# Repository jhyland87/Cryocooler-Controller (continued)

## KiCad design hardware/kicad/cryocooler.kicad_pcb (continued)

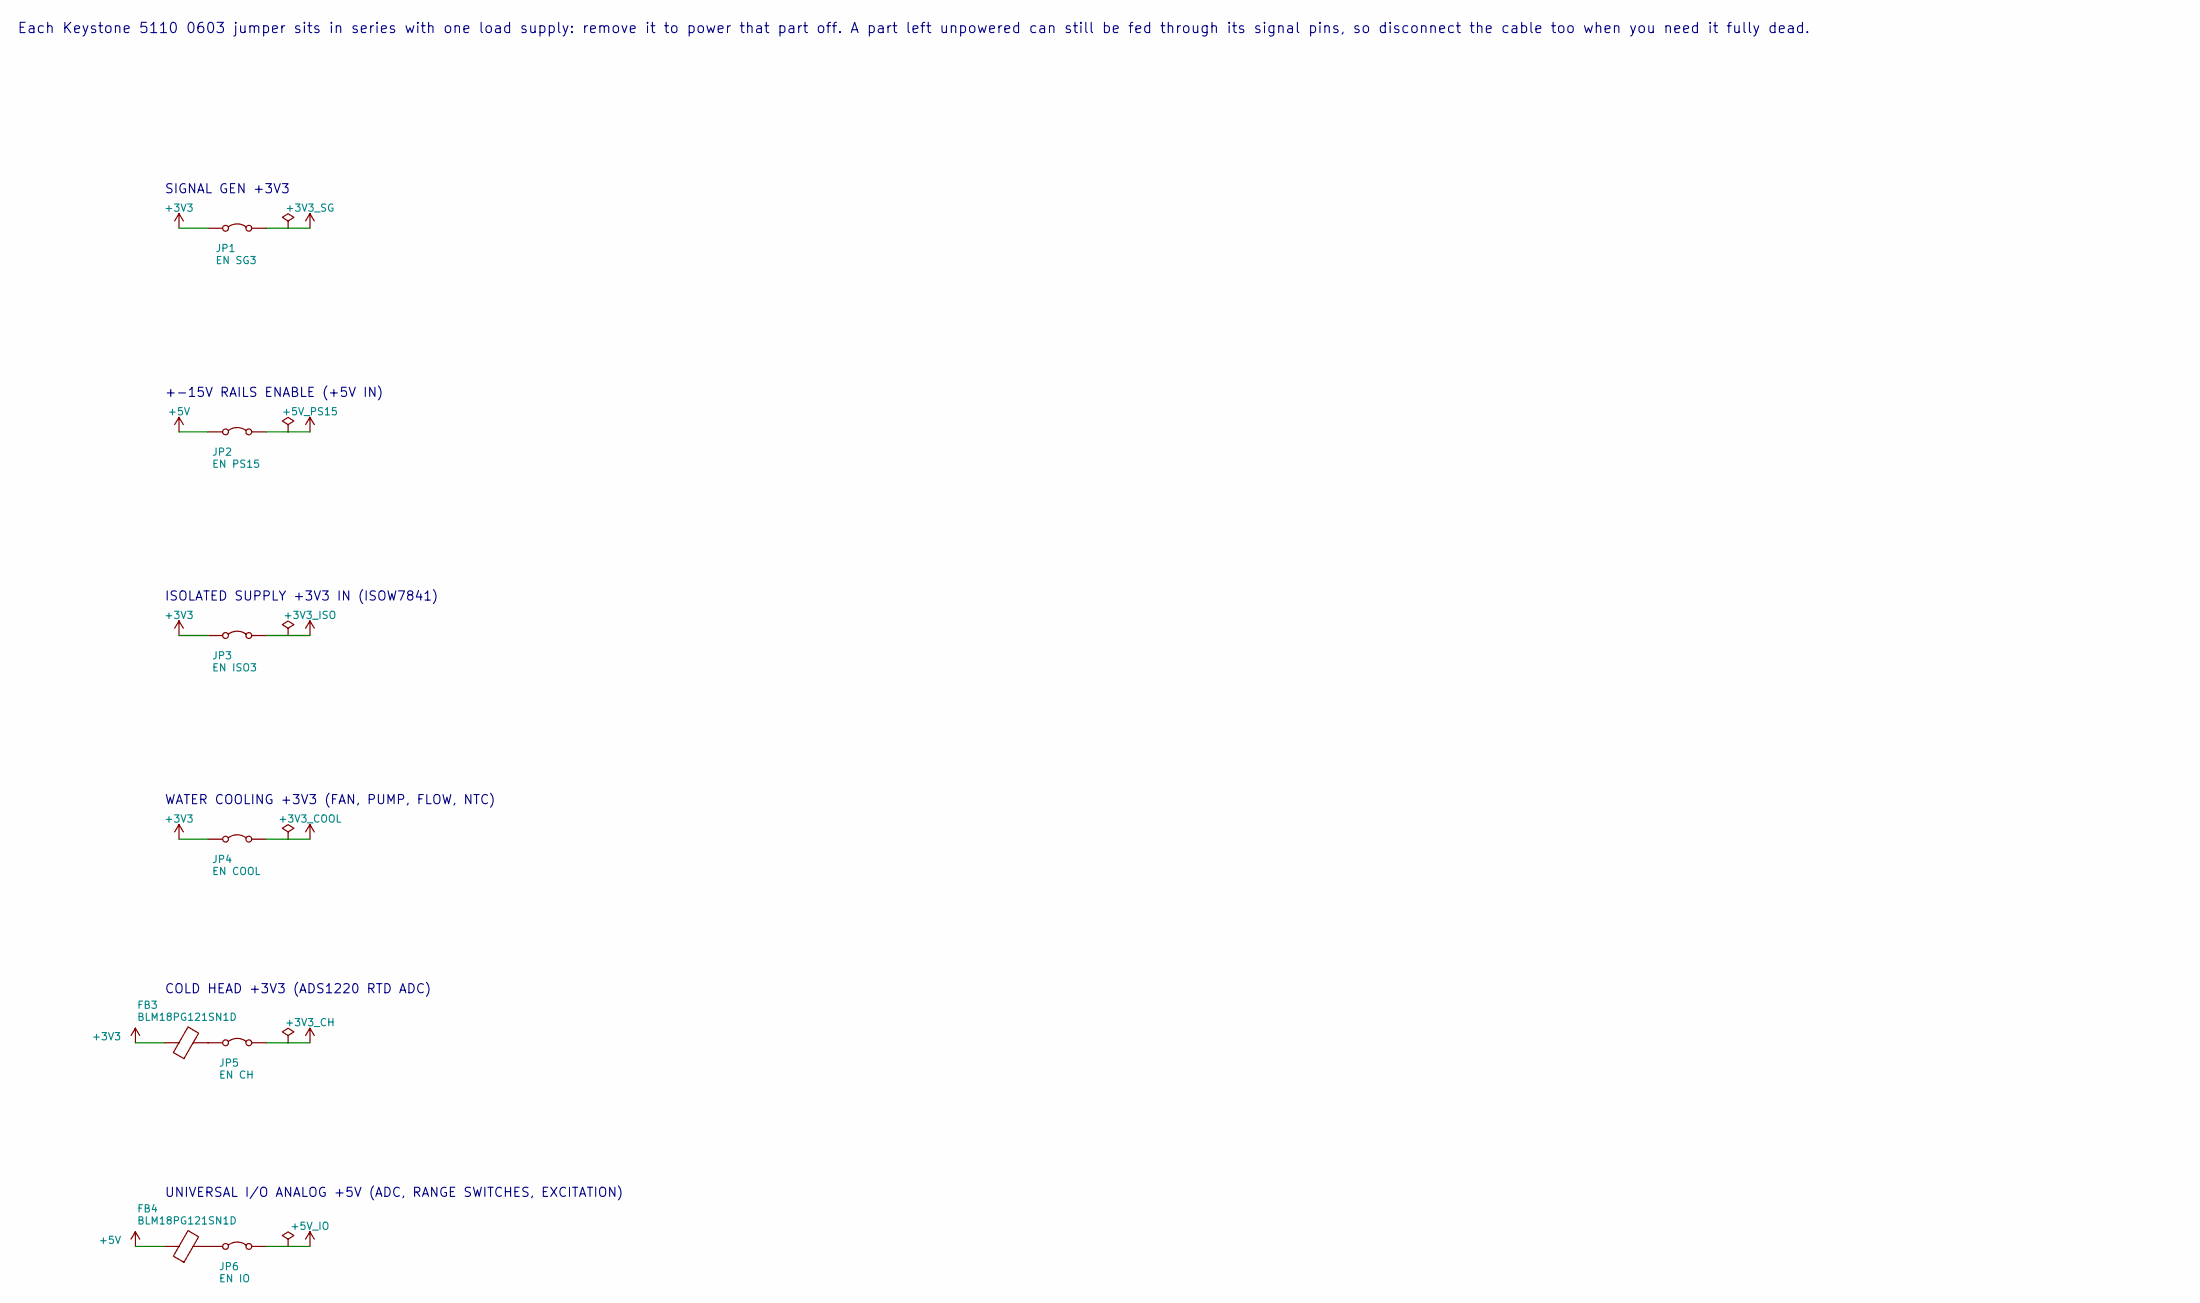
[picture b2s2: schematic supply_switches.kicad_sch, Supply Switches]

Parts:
FB3, FB4: BLM18PG121SN1D; L_0603_1608Metric
JP1: EN SG3; R_0603_1608Metric
JP2: EN PS15; R_0603_1608Metric
JP3: EN ISO3; R_0603_1608Metric
JP4: EN COOL; R_0603_1608Metric
JP5: EN CH; R_0603_1608Metric
JP6: EN IO; R_0603_1608Metric

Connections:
+3V3: FB3.1, JP1.1 (A), JP3.1 (A), JP4.1 (A); also elsewhere on the board
+3V3_CH: JP5.2 (B); also elsewhere on the board
+3V3_COOL: JP4.2 (B); also elsewhere on the board
+3V3_ISO: JP3.2 (B); also elsewhere on the board
+3V3_SG: JP1.2 (B); also elsewhere on the board
+5V: FB4.1, JP2.1 (A); also elsewhere on the board
+5V_IO: JP6.2 (B); also elsewhere on the board
+5V_PS15: JP2.2 (B); also elsewhere on the board
unnamed: FB3.2, JP5.1 (A)
unnamed: FB4.2, JP6.1 (A)

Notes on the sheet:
ISOLATED SUPPLY +3V3 IN (ISOW7841)
+-15V RAILS ENABLE (+5V IN)
Each Keystone 5110 0603 jumper sits in series with one load supply: remove it to power that part off. A part left unpowered can still be fed through its signal pins, so disconnect the cable too when you need it fully dead.
SIGNAL GEN +3V3
WATER COOLING +3V3 (FAN, PUMP, FLOW, NTC)
COLD HEAD +3V3 (ADS1220 RTD ADC)
UNIVERSAL I/O ANALOG +5V (ADC, RANGE SWITCHES, EXCITATION)

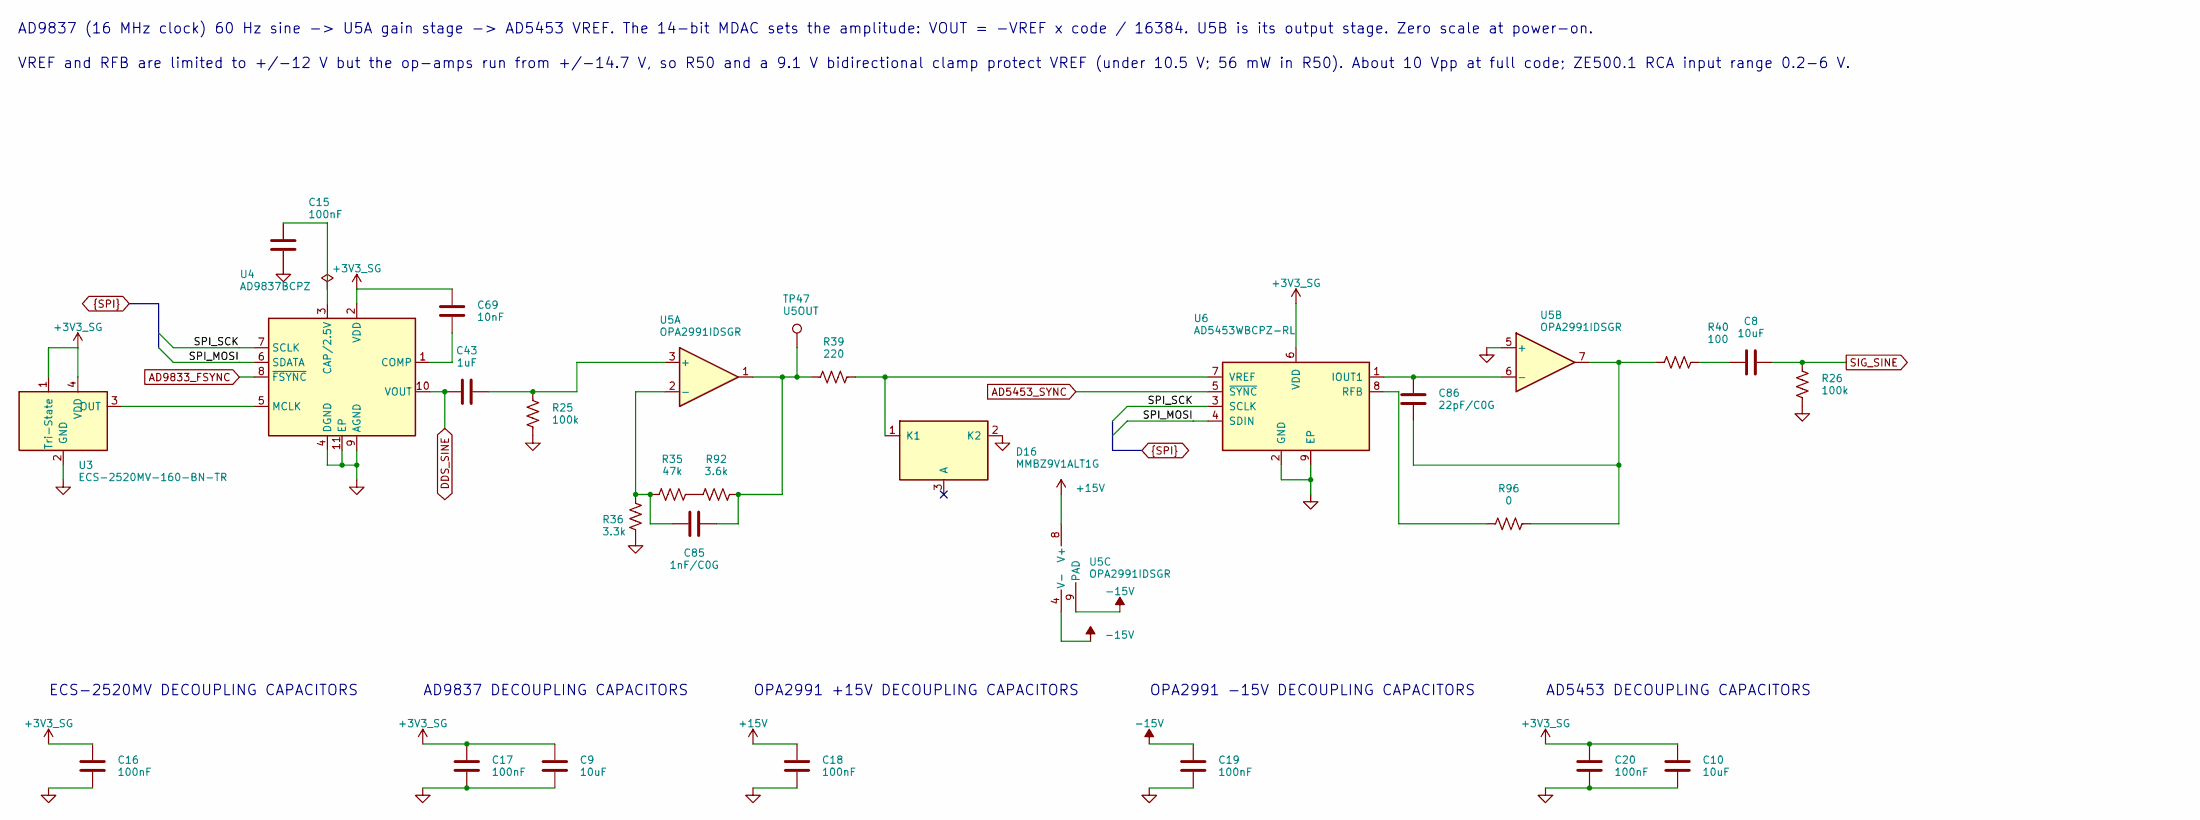
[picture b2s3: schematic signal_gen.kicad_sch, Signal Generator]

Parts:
C8, C9, C10: 10uF; C_0805_2012Metric
C15, C16, C17, C18, C19, C20: 100nF; C_0402_1005Metric
C43: 1uF; C_0603_1608Metric
C69: 10nF; C_0402_1005Metric
C85: 1nF/C0G; C_0402_1005Metric
C86: 22pF/C0G; C_0402_1005Metric
D16: MMBZ9V1ALT1G; SOT-23
R25, R26: 100k; R_0402_1005Metric
R35: 47k; R_0402_1005Metric
R36: 3.3k; R_0402_1005Metric
R39: 220; R_0402_1005Metric
R40: 100; R_0402_1005Metric
R92: 3.6k; R_1206_or_Bourns_3313J
R96: 0; R_1206_or_Bourns_3313J
TP47: U5OUT; TestPoint_Pad_D1.0mm
U3: ECS-2520MV-160-BN-TR; Oscillator_SMD_ECS_2520MV-xxx-xx-4Pin_2.5x2.0mm
U4: AD9837BCPZ; LFCSP-WD-10-1EP_3x3mm_P0.5mm_EP1.64x2.38mm
U5: OPA2991IDSGR; TI_DSG0008A_WSON-8-1EP_2x2mm_P0.5mm_EP0.9x1.6mm
U6: AD5453WBCPZ-RL; VSON-8-1EP_3x3mm_P0.65mm_EP1.65x2.4mm

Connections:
+3V3_SG: C9.1, C10.1, C16.1, C17.1, C20.1, C69.1, U3.1 (Tri-State), U3.4 (VDD), U4.2 (VDD), U6.6 (VDD); also elsewhere on the board
+15V: C18.1, U5.8 (V+); also elsewhere on the board
-15V: C19.1, U5.4 (V-), U5.9 (PAD); also elsewhere on the board
/DDS_SINE: C43.1, U4.10 (VOUT); also elsewhere on the board
/SIG_SINE: C8.2, R26.1; also elsewhere on the board
/~AD5453_SYNC: U6.5 (~SYNC); also elsewhere on the board
/~AD9833_FSYNC: U4.8 (~FSYNC); also elsewhere on the board
GND: C9.2, C10.2, C15.2, C16.2, C17.2, C18.2, C19.2, C20.2, D16.2 (K2), R25.2, R26.2, R36.2, U3.2 (GND), U4.4 (DGND), U4.9 (AGND), U4.11 (EP), U5.5 (+), U6.2 (GND), U6.9 (EP); also elsewhere on the board
unnamed: C8.1, R40.2
unnamed: C85.2, R39.1, R92.2, TP47.1, U5.1
unnamed: C86.2, R40.1, R96.2, U5.7
unnamed: D16.1 (K1), R39.2, U6.7 (VREF)
unnamed: R35.2, R92.1
unnamed: U3.3 (OUT), U4.5 (MCLK)
unnamed: C15.1, U4.3 (CAP/2.5V)
unnamed: C69.2, U4.1 (COMP)
unnamed: C43.2, R25.1, U5.3 (+)
unnamed: C85.1, R35.1, R36.1, U5.2 (-)
unnamed: C86.1, U5.6 (-), U6.1 (IOUT1)
unnamed: R96.1, U6.8 (RFB)
SPI_MOSI: U4.6 (SDATA), U6.4 (SDIN); also elsewhere on the board
SPI_SCK: U4.7 (SCLK), U6.3 (SCLK); also elsewhere on the board

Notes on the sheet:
OPA2991 +15V DECOUPLING CAPACITORS
AD9837 (16 MHz clock) 60 Hz sine -> U5A gain stage -> AD5453 VREF. The 14-bit MDAC sets the amplitude: VOUT = -VREF x code / 16384. U5B is its output stage. Zero scale at power-on.
AD9837 DECOUPLING CAPACITORS
VREF and RFB are limited to +/-12 V but the op-amps run from +/-14.7 V, so R50 and a 9.1 V bidirectional clamp protect VREF (under 10.5 V; 56 mW in R50). About 10 Vpp at full code; ZE500.1 RCA input range 0.2-6 V.
ECS-2520MV DECOUPLING CAPACITORS
AD5453 DECOUPLING CAPACITORS
OPA2991 -15V DECOUPLING CAPACITORS

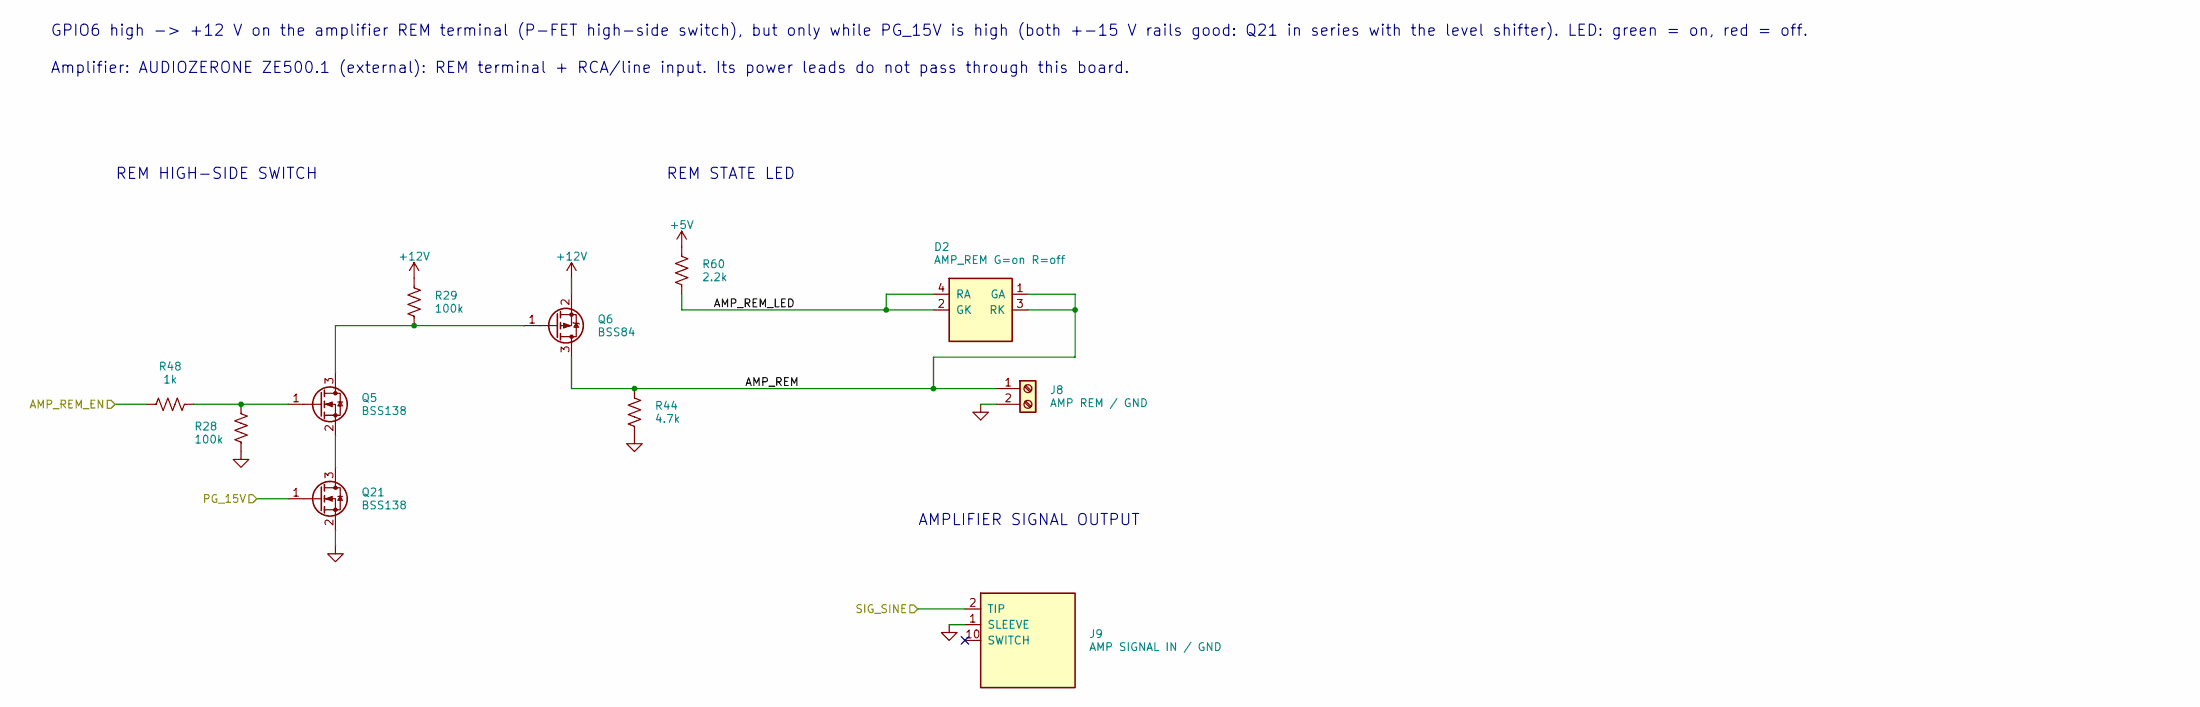
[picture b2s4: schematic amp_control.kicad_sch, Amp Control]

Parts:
D2: AMP_REM G=on R=off; LED_Kingbright_APGB0607
J8: AMP REM / GND; PhoenixContact_MC_0,5_2-G-2,54_SMD_1x02_P2.54mm_Horizontal
J9: AMP SIGNAL IN / GND; SameSky_MJ-3523-SMT-TR_3.5mm_Horizontal_SMD
Q5, Q21: BSS138; SOT-23
Q6: BSS84; SOT-23
R28, R29: 100k; R_0402_1005Metric
R44: 4.7k; R_0402_1005Metric
R48: 1k; R_0402_1005Metric
R60: 2.2k; R_0402_1005Metric

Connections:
+5V: R60.1; also elsewhere on the board
+12V: Q6.2 (S), R29.1; also elsewhere on the board
/AMP_REM_EN: R48.1; also elsewhere on the board
/Amp Control/AMP_REM: D2.1 (GA), D2.3 (RK), J8.1, Q6.3 (D), R44.1
/Amp Control/AMP_REM_LED: D2.2 (GK), D2.4 (RA), R60.2
/PG_15V: Q21.1 (G); also elsewhere on the board
/SIG_SINE: J9.2 (TIP); also elsewhere on the board
GND: J8.2, J9.1 (SLEEVE), Q21.2 (S), R28.2, R44.2; also elsewhere on the board
unnamed: Q5.3 (D), Q6.1 (G), R29.2
unnamed: Q5.1 (G), R28.1, R48.2
unnamed: Q5.2 (S), Q21.3 (D)

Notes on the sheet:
GPIO6 high -> +12 V on the amplifier REM terminal (P-FET high-side switch), but only while PG_15V is high (both +-15 V rails good: Q21 in series with the level shifter). LED: green = on, red = off.
REM HIGH-SIDE SWITCH
AMPLIFIER SIGNAL OUTPUT
REM STATE LED
Amplifier: AUDIOZERONE ZE500.1 (external): REM terminal + RCA/line input. Its power leads do not pass through this board.

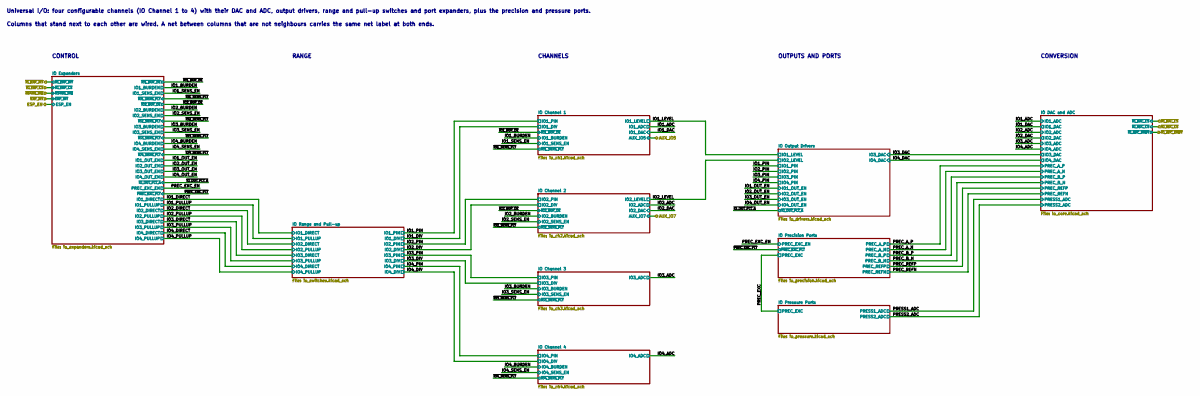
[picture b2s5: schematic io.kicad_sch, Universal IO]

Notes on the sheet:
Columns that stand next to each other are wired. A net between columns that are not neighbours carries the same net label at both ends.
Universal I/O: four configurable channels (IO Channel 1 to 4) with their DAC and ADC, output drivers, range and pull-up switches and port expanders, plus the precision and pressure ports.
CHANNELS
OUTPUTS AND PORTS
RANGE
CONVERSION
CONTROL

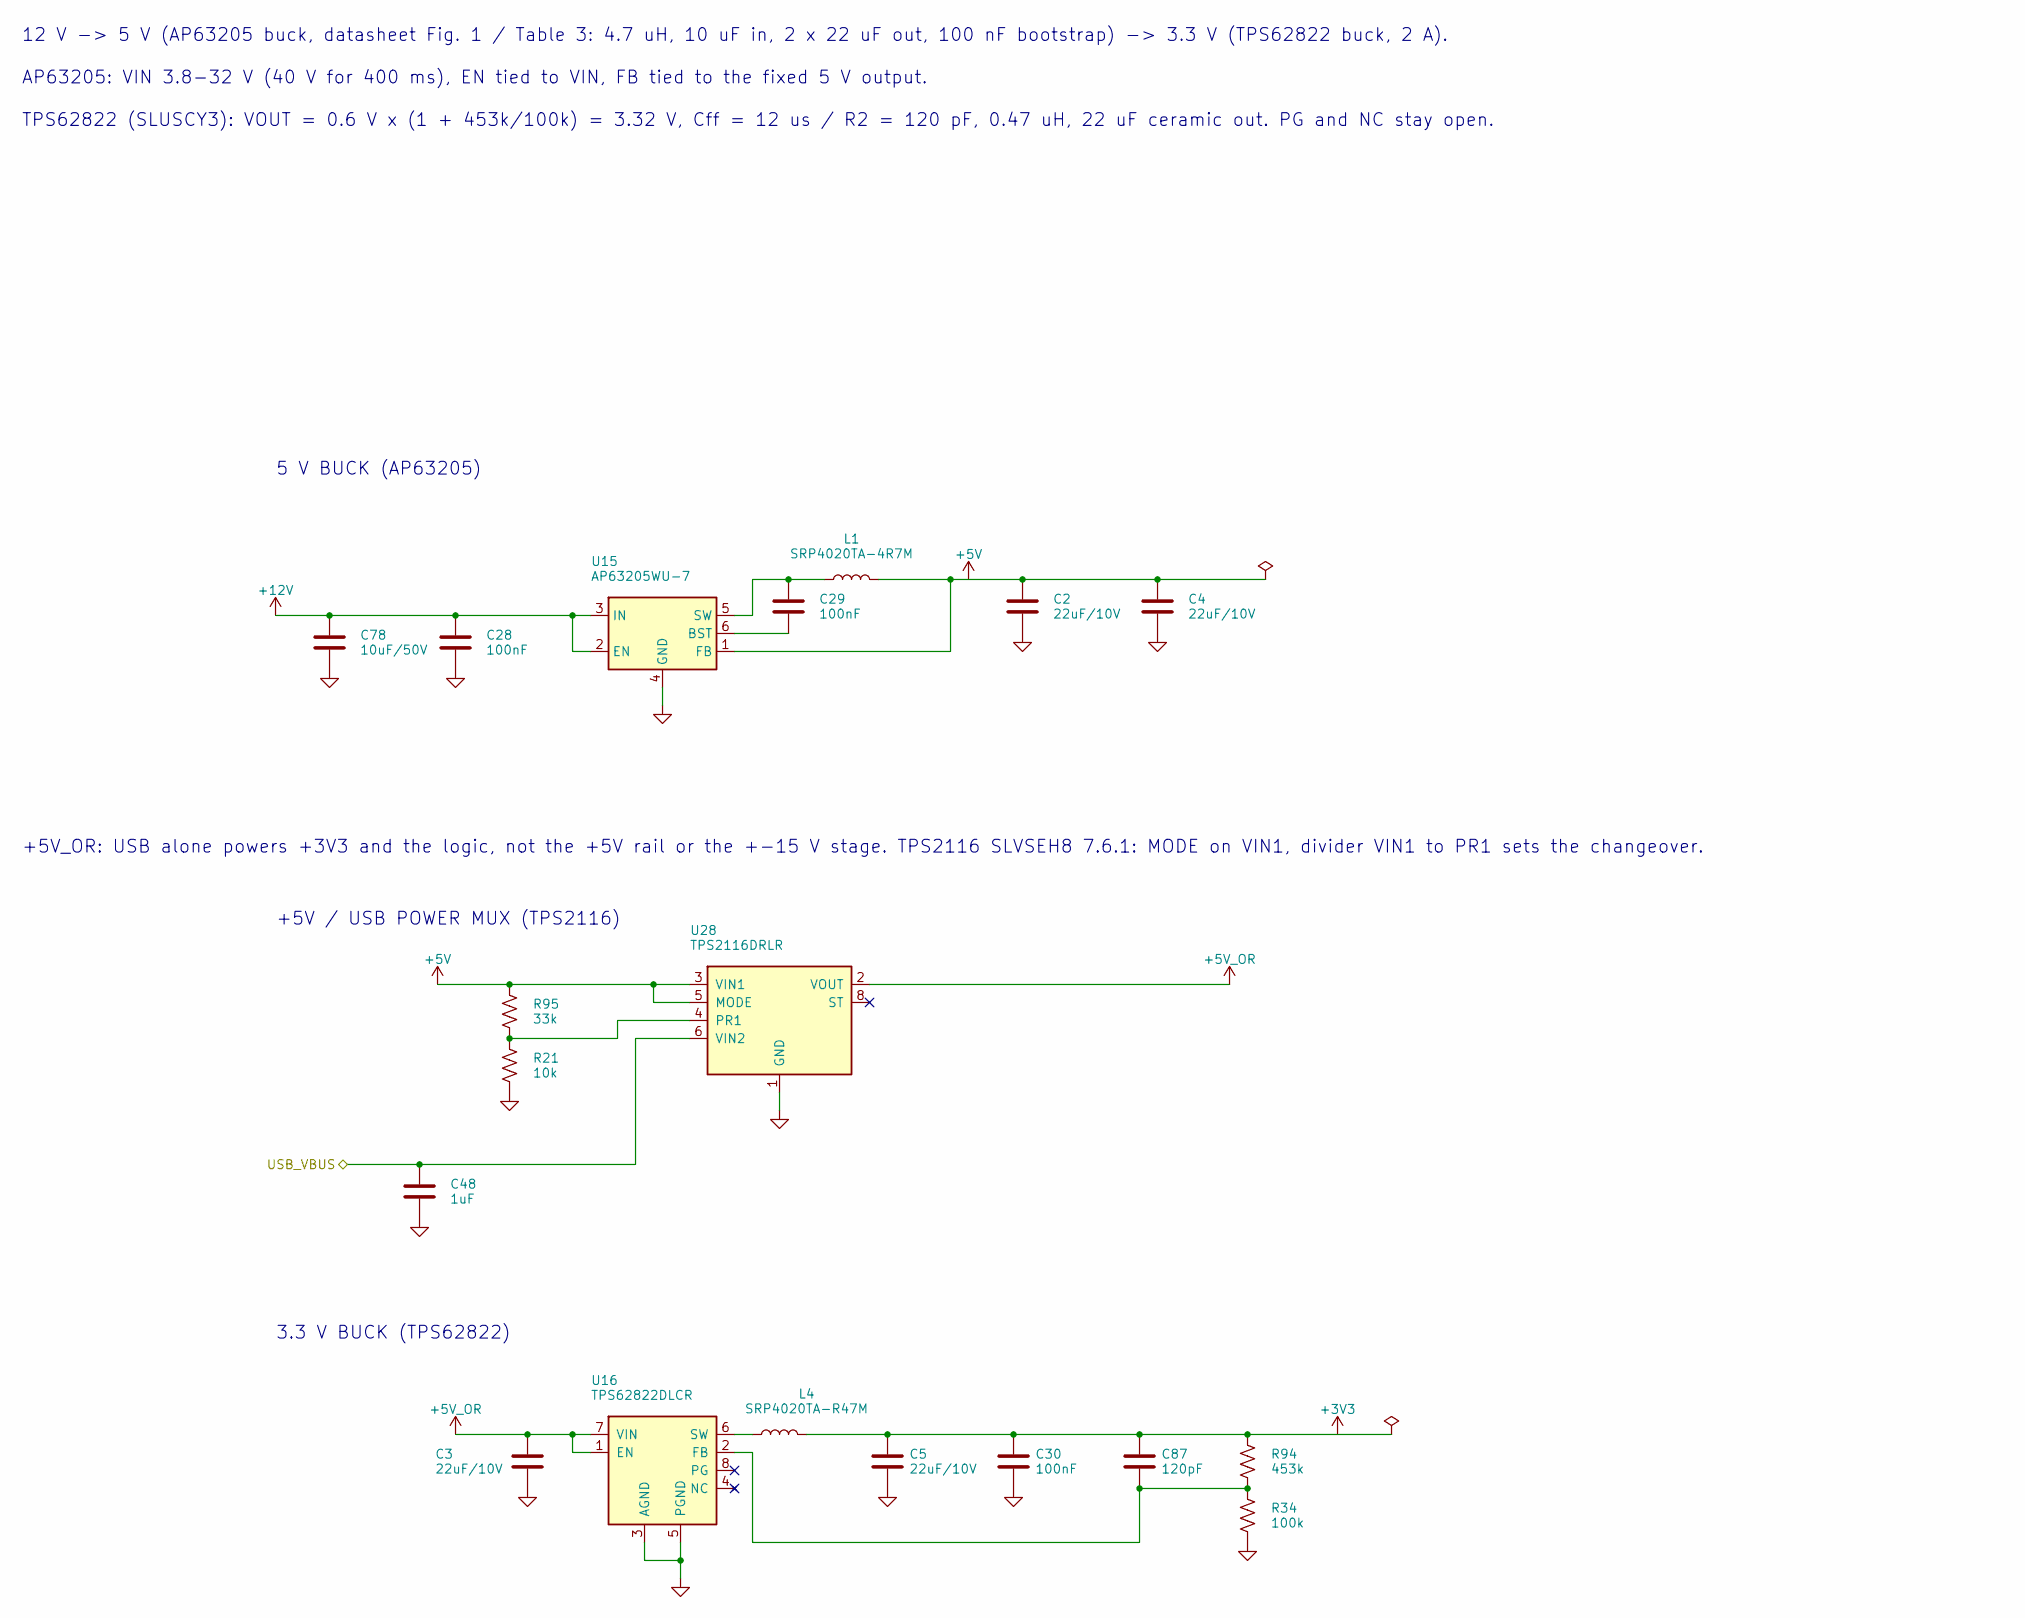
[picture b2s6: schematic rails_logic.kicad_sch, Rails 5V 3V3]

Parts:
C2, C3, C4, C5: 22uF/10V; C_1206_3216Metric
C28, C29, C30: 100nF; C_0402_1005Metric
C48: 1uF; C_0603_1608Metric
C78: 10uF/50V; C_1206_3216Metric
C87: 120pF; C_0402_1005Metric
L1: SRP4020TA-4R7M; L_Bourns_SRP4020TA
L4: SRP4020TA-R47M; L_Bourns_SRP4020TA
R21: 10k; R_0402_1005Metric
R34: 100k; R_0402_1005Metric
R94: 453k; R_0402_1005Metric
R95: 33k; R_0402_1005Metric
U15: AP63205WU-7; TSOT-23-6
U16: TPS62822DLCR; Texas_VSON-HR-8_1.5x2mm_P0.5mm
U28: TPS2116DRLR; SOT-583-8

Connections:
+3V3: C5.1, C30.1, C87.1, L4.2, R94.1; also elsewhere on the board
+5V: C2.1, C4.1, L1.2, R95.1, U15.1 (FB), U28.3 (VIN1), U28.5 (MODE); also elsewhere on the board
+5V_OR: C3.1, U16.1 (EN), U16.7 (VIN), U28.2 (VOUT), U28.7 (VOUT)
+12V: C28.1, C78.1, U15.2 (EN), U15.3 (IN); also elsewhere on the board
/USB_VBUS: C48.1, U28.6 (VIN2); also elsewhere on the board
GND: C2.2, C3.2, C4.2, C5.2, C28.2, C30.2, C48.2, C78.2, R21.2, R34.2, U15.4 (GND), U16.3 (AGND), U16.5 (PGND), U28.1 (GND); also elsewhere on the board
unnamed: C29.2, U15.6 (BST)
unnamed: C29.1, L1.1, U15.5 (SW)
unnamed: C87.2, R34.1, R94.2, U16.2 (FB)
unnamed: L4.1, U16.6 (SW)
unnamed: R21.1, R95.2, U28.4 (PR1)

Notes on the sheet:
+5V / USB POWER MUX (TPS2116)
TPS62822 (SLUSCY3): VOUT = 0.6 V x (1 + 453k/100k) = 3.32 V, Cff = 12 us / R2 = 120 pF, 0.47 uH, 22 uF ceramic out. PG and NC stay open.
AP63205: VIN 3.8-32 V (40 V for 400 ms), EN tied to VIN, FB tied to the fixed 5 V output.
5 V BUCK (AP63205)
3.3 V BUCK (TPS62822)
12 V -> 5 V (AP63205 buck, datasheet Fig. 1 / Table 3: 4.7 uH, 10 uF in, 2 x 22 uF out, 100 nF bootstrap) -> 3.3 V (TPS62822 buck, 2 A).
+5V_OR: USB alone powers +3V3 and the logic, not the +5V rail or the +-15 V stage. TPS2116 SLVSEH8 7.6.1: MODE on VIN1, divider VIN1 to PR1 sets the changeover.

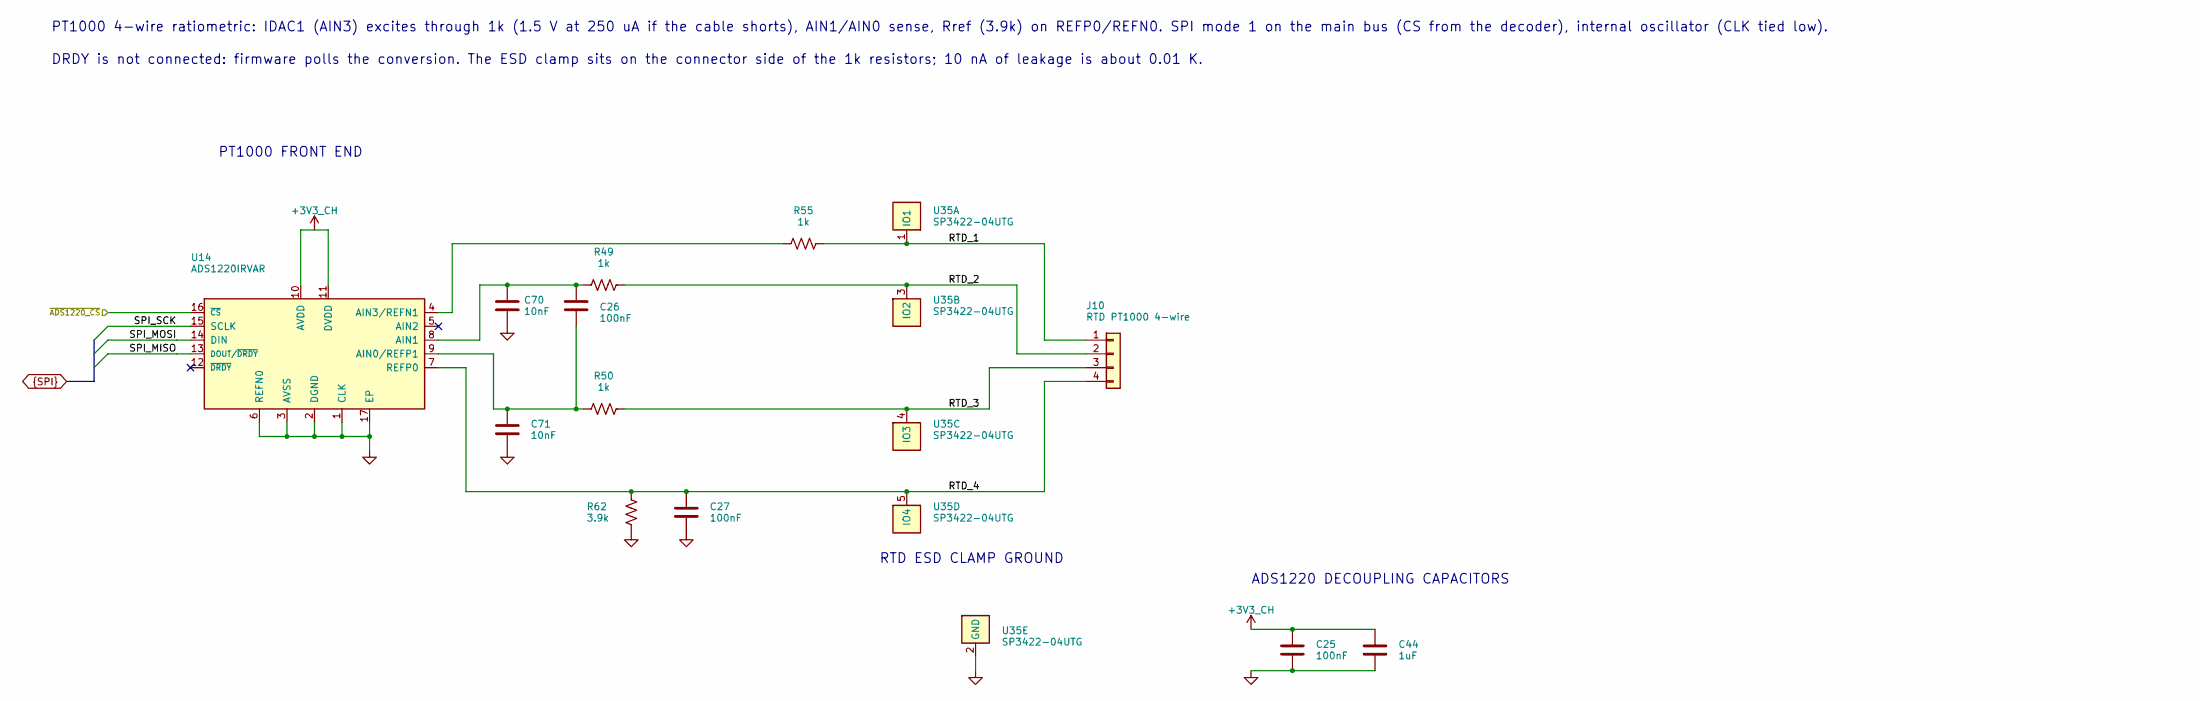
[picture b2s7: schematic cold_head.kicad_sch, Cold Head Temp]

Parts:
C25, C26, C27: 100nF; C_0402_1005Metric
C44: 1uF; C_0603_1608Metric
C70, C71: 10nF; C_0402_1005Metric
J10: RTD PT1000 4-wire; Adafruit_4392_JST-PH_1x04_P2.00mm_Horizontal_SMD
R49, R50, R55: 1k; R_0402_1005Metric
R62: 3.9k; R_0402_1005Metric
U14: ADS1220IRVAR; Texas_RVA_VQFN-16-1EP_3.5x3.5mm_P0.5mm_EP2.14x2.14mm
U35: SP3422-04UTG; Littelfuse_DFN-5_1.0x0.6mm_P0.35mm

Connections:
+3V3_CH: C25.1, C44.1, U14.10 (AVDD), U14.11 (DVDD); also elsewhere on the board
/Cold Head Temp/RTD_1: J10.1, R55.2, U35.1 (IO1)
/Cold Head Temp/RTD_2: J10.2, R49.2, U35.3 (IO2)
/Cold Head Temp/RTD_3: J10.3, R50.2, U35.4 (IO3)
/Cold Head Temp/RTD_4: C27.1, J10.4, R62.1, U14.7 (REFP0), U35.5 (IO4)
/~ADS1220_CS: U14.16 (~CS); also elsewhere on the board
GND: C25.2, C27.2, C44.2, C70.2, C71.2, R62.2, U14.1 (CLK), U14.2 (DGND), U14.3 (AVSS), U14.6 (REFN0), U14.17 (EP), U35.2 (GND); also elsewhere on the board
unnamed: C26.2, C71.1, R50.1, U14.9 (AIN0/REFP1)
unnamed: C26.1, C70.1, R49.1, U14.8 (AIN1)
unnamed: R55.1, U14.4 (AIN3/REFN1)
SPI_MISO: U14.13 (DOUT/~DRDY); also elsewhere on the board
SPI_MOSI: U14.14 (DIN); also elsewhere on the board
SPI_SCK: U14.15 (SCLK); also elsewhere on the board

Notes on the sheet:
PT1000 4-wire ratiometric: IDAC1 (AIN3) excites through 1k (1.5 V at 250 uA if the cable shorts), AIN1/AIN0 sense, Rref (3.9k) on REFP0/REFN0. SPI mode 1 on the main bus (CS from the decoder), internal oscillator (CLK tied low).
DRDY is not connected: firmware polls the conversion. The ESD clamp sits on the connector side of the 1k resistors; 10 nA of leakage is about 0.01 K.
RTD ESD CLAMP GROUND
ADS1220 DECOUPLING CAPACITORS
PT1000 FRONT END

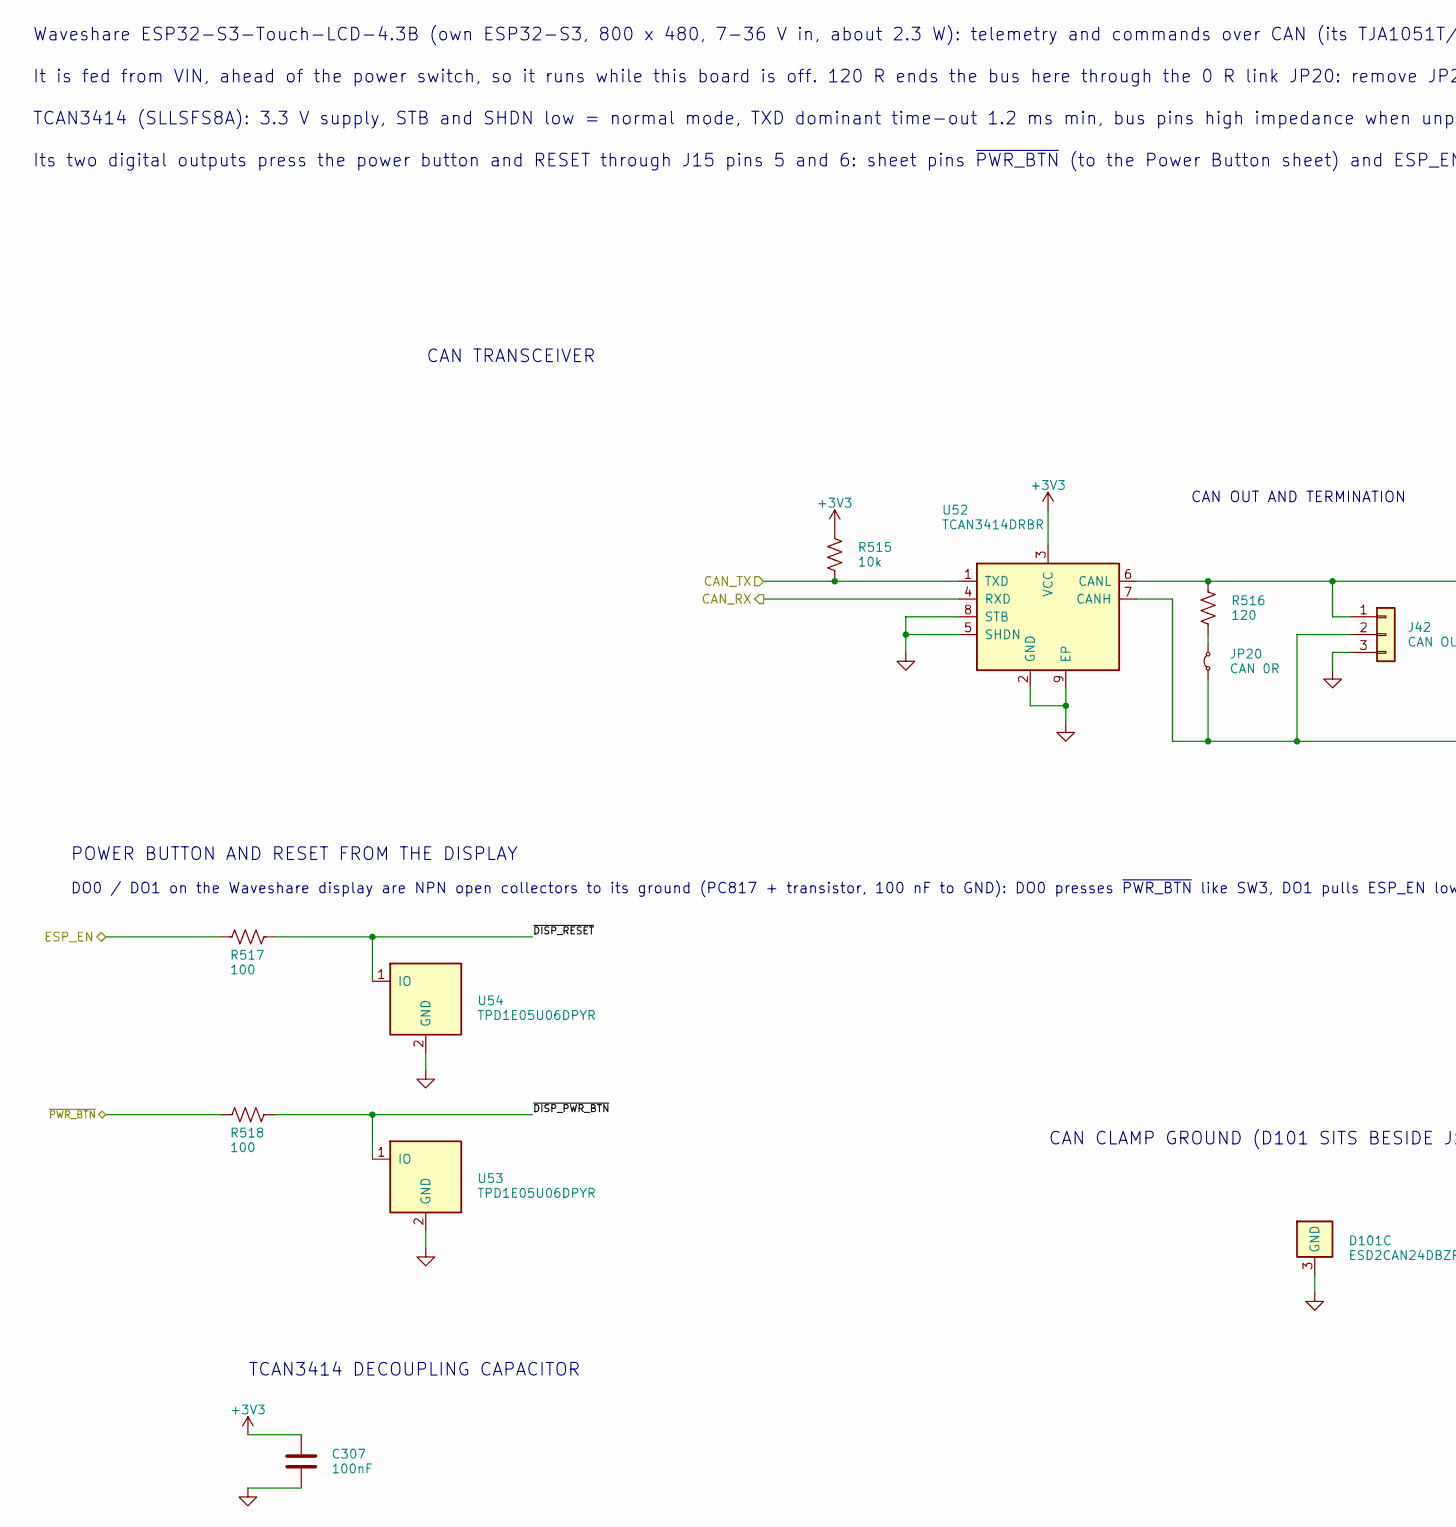
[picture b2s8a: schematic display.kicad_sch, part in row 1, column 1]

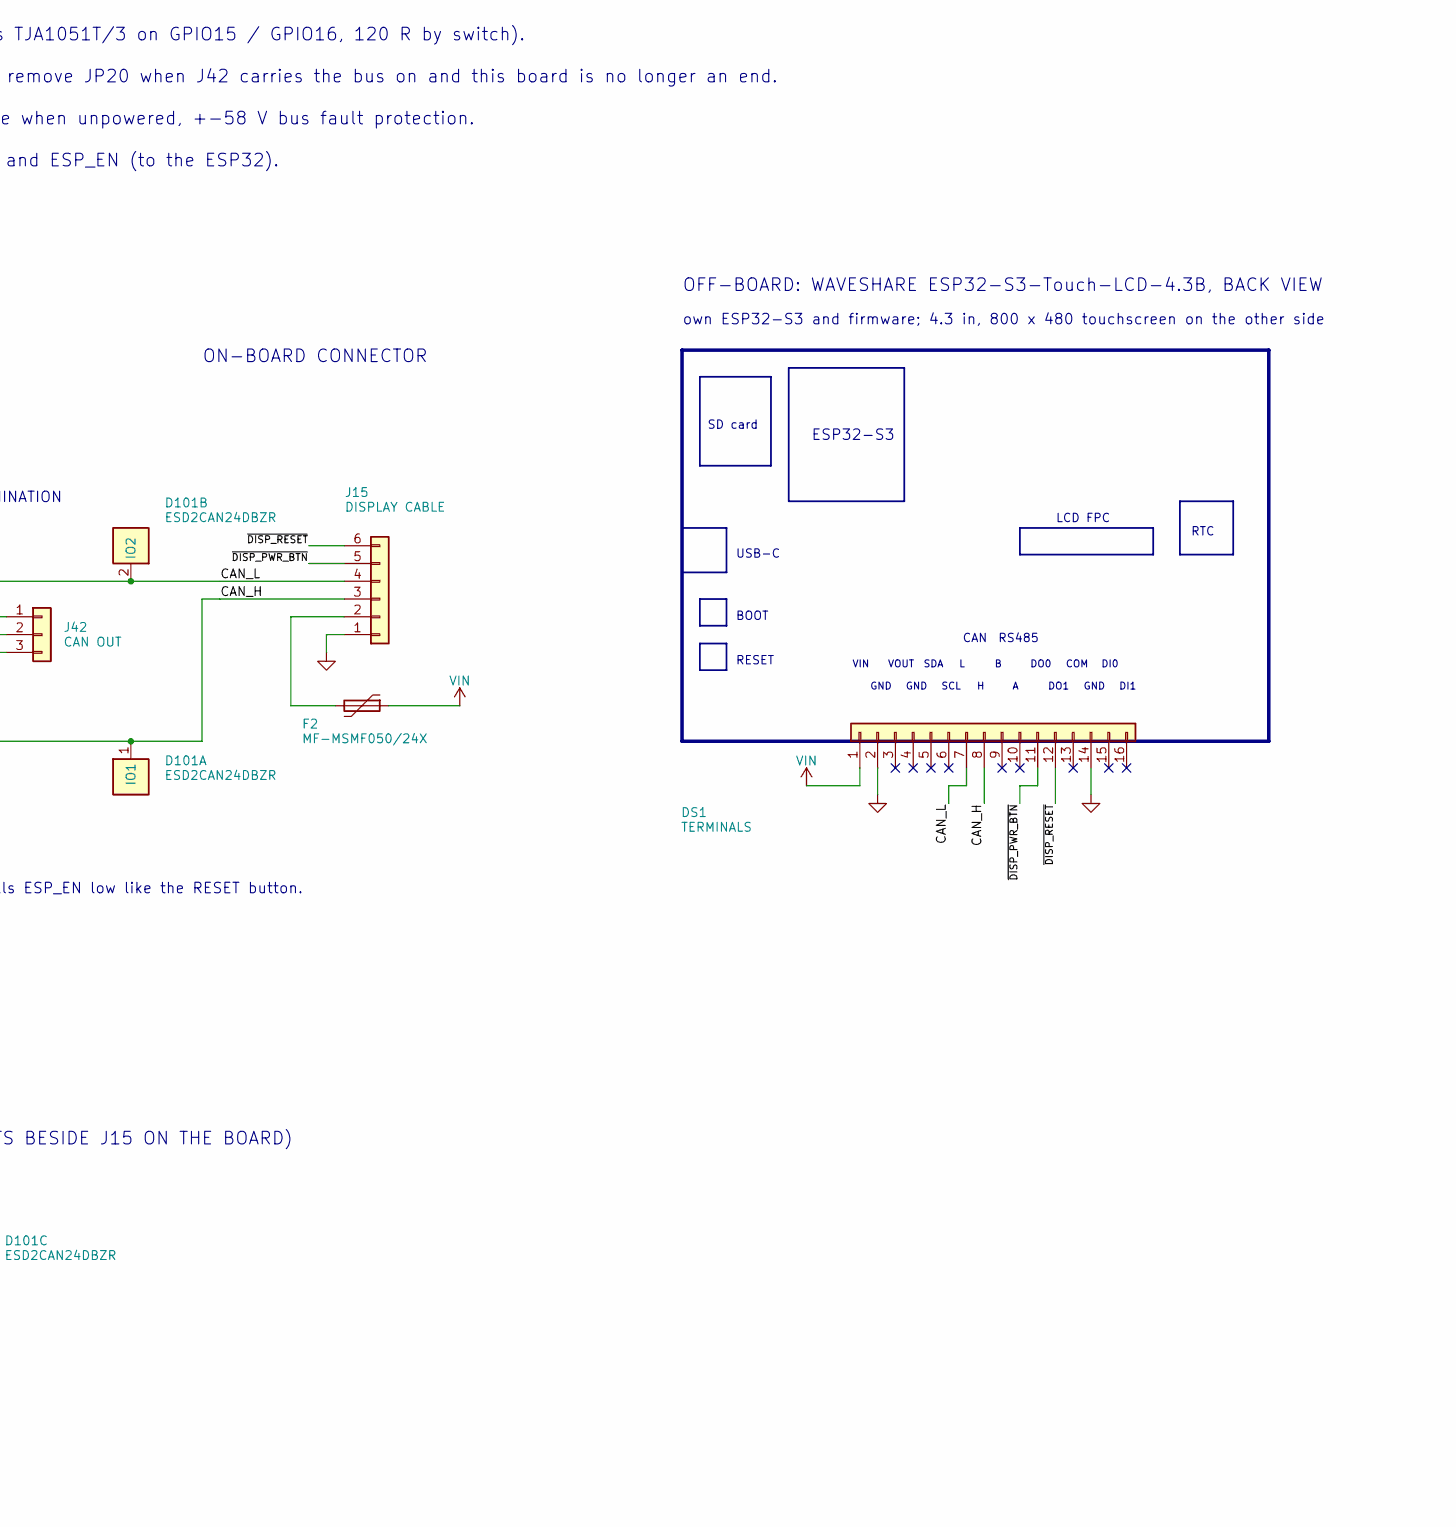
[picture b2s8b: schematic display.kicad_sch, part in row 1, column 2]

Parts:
C307: 100nF; C_0402_1005Metric
D101: ESD2CAN24DBZR; SOT-23
DS1: TERMINALS
F2: MF-MSMF050/24X; Fuse_1812_4532Metric
J15: DISPLAY CABLE; JST_PH_B6B-PH-SM4-TB_1x06-1MP_P2.00mm_Vertical
J42: CAN OUT; JST_PH_B3B-PH-SM4-TB_1x03-1MP_P2.00mm_Vertical
JP20: CAN 0R; R_0603_1608Metric
R515: 10k; R_0402_1005Metric
R516: 120; R_1206_3216Metric
R517, R518: 100; R_0402_1005Metric
U52: TCAN3414DRBR; VSON-8-1EP_3x3mm_P0.65mm_EP1.65x2.4mm
U53, U54: TPD1E05U06DPYR; Texas_DPY0002A_0.6x1mm_P0.65mm

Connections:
+3V3: C307.1, R515.1, U52.3 (VCC); also elsewhere on the board
/CAN_RX: U52.4 (RXD); also elsewhere on the board
/CAN_TX: R515.2, U52.1 (TXD); also elsewhere on the board
/Display/CAN_H: D101.1 (IO1), DS1.8, J15.3, J42.2, JP20.1 (A), U52.7 (CANH)
/Display/CAN_L: D101.2 (IO2), DS1.7, J15.4, J42.1, R516.2, U52.6 (CANL)
/Display/~DISP_PWR_BTN: DS1.11, J15.5, R518.2, U53.1 (IO)
/Display/~DISP_RESET: DS1.12, J15.6, R517.2, U54.1 (IO)
/ESP_EN: R517.1; also elsewhere on the board
/~PWR_BTN: R518.1; also elsewhere on the board
GND: C307.2, D101.3 (GND), DS1.2, DS1.14, J15.1, J42.3, U52.2 (GND), U52.5 (SHDN), U52.8 (STB), U52.9 (EP), U53.2 (GND), U54.2 (GND); also elsewhere on the board
unnamed: F2.2, J15.2
unnamed: JP20.2 (B), R516.1
VIN: DS1.1, F2.1; also elsewhere on the board

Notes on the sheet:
CAN CLAMP GROUND (D101 SITS BESIDE J15 ON THE BOARD)
Its two digital outputs press the power button and RESET through J15 pins 5 and 6: sheet pins ~{PWR_BTN} (to the Power Button sheet) and ESP_EN (to the ESP32).
DO0
GND
DO1
SDA
SCL
COM
CAN OUT AND TERMINATION
ON-BOARD CONNECTOR
LCD FPC
OFF-BOARD: WAVESHARE ESP32-S3-Touch-LCD-4.3B, BACK VIEW
BOOT
own ESP32-S3 and firmware; 4.3 in, 800 x 480 touchscreen on the other side
RTC
TCAN3414 (SLLSFS8A): 3.3 V supply, STB and SHDN low = normal mode, TXD dominant time-out 1.2 ms min, bus pins high impedance when unpowered, +-58 V bus fault protection.
VIN
CAN TRANSCEIVER
DI1
POWER BUTTON AND RESET FROM THE DISPLAY
ESP32-S3
It is fed from VIN, ahead of the power switch, so it runs while this board is off. 120 R ends the bus here through the 0 R link JP20: remove JP20 when J42 carries the bus on and this board is no longer an end.
DI0
DO0 / DO1 on the Waveshare display are NPN open collectors to its ground (PC817 + transistor, 100 nF to GND): DO0 presses ~{PWR_BTN} like SW3, DO1 pulls ESP_EN low like the RESET button.
RS485
USB-C
VOUT
CAN
RESET
SD card
TCAN3414 DECOUPLING CAPACITOR
Waveshare ESP32-S3-Touch-LCD-4.3B (own ESP32-S3, 800 x 480, 7-36 V in, about 2.3 W): telemetry and commands over CAN (its TJA1051T/3 on GPIO15 / GPIO16, 120 R by switch).

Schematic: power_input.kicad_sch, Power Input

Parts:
C65: 100uF/35V; CP_Elec_8x10
C67: 100nF; C_0805_2012Metric
D1: SMBJ16A; D_SMB
F1: 10A backup; Fuse_Littelfuse-NANO2-451_453
J2: 12V IN (ATX 4-PIN); Molex_Mini-Fit_Jr_5569-04A2_2x02_P4.20mm_Horizontal

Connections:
GND: C65.2, C67.2, D1.2 (A2), J2.1 (COM), J2.2 (COM); also elsewhere on the board
unnamed: F1.1, J2.3 (+12V), J2.4 (+12V)
VIN: C65.1, C67.1, D1.1 (A1), F1.2; also elsewhere on the board

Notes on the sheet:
Sized for 10 A (about 7.5 A continuous): fans and pump up to 4.2 A plus the I/O. F1 is a backup only: add an inline high-breaking-capacity fuse at the PSU end. Reverse polarity: the TVS forward-clamps and blows the fuse.
12 V input from a Dell XYK93 (DPS-2000EB class, ~12.2 V, ~160 A available): use the main 12 V rail with PS_ON held low.

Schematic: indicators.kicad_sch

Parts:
C33, C34: 100nF; C_0402_1005Metric
D13: WS2812B-2020; LED_WS2812B-2020_PLCC4_2.0x2.0mm
R10: 10k; R_0402_1005Metric
R85: 330; R_0402_1005Metric
U24: 74AHCT1G125GM; Nexperia_XSON-6_SOT886_1.0x1.45mm_P0.5mm

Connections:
+5V: C33.1, C34.1, D13.4 (VDD), U24.6 (VCC); also elsewhere on the board
/STATUS_RGB: R10.1, U24.2 (A); also elsewhere on the board
GND: C33.2, C34.2, D13.2 (VSS), R10.2, U24.1 (~OE), U24.3 (GND); also elsewhere on the board
unnamed: D13.3 (DIN), R85.2
unnamed: R85.1, U24.4 (Y)

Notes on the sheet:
WS2812B-2020 status LED on GPIO38 via a 74AHCT1G125GM 3.3 V -> 5 V level shifter. Works without the SPI bus, so it can show faults the bus would hide.
WS2812B-2020 DECOUPLING CAPACITORS
74AHCT1G125GM DECOUPLING CAPACITORS
STATUS LED
